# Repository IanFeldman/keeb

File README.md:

# A minimal ergo keyboard
Low profile, split, ortholinear, 34-key layout staggered to my natural finger rest positions. Designed for Gateron KS-33 Red swiches and DSA keycaps.
See write-up [here](https://ianfeldman.dev/projects/keyboard/).
<br><br>

## Features
- N-key rollover
- Efficient matrixless polling
- Lightweight and portable
- Serial communication between splits
- USB-C host connection

## Hardware Build Instructions
- Order and assemble PCB's
  - Reflow recommended for all surface mount components except SPI headers, TRRS jack, and crystal oscillator.
  - On hardware version 1.1, there are duplicate C2 and C3 traces. Only solder one C2 and one C3.
- Configure programming setup using In-system programmer (ensure shared ground)
- Power on PCB through USB-C connector
<br><br> _Note: only one PCB can be flashed at a time_

## Software Build and Flash Instructions (Linux)
```sh
# Install dependencies
sudo apt install gcc-avr avr-libc avrdude make

# Clone this repo
git clone https://github.com/IanFeldman/keeb.git
cd keeb

# Compile left or right half
make [left] [right]

# Update makefile targets 'fuses' and 'flash' as needed for your ISP device
# Set fuses with ISP (first time only)
make fuses

# Flash keyboard with ISP
make flash
```

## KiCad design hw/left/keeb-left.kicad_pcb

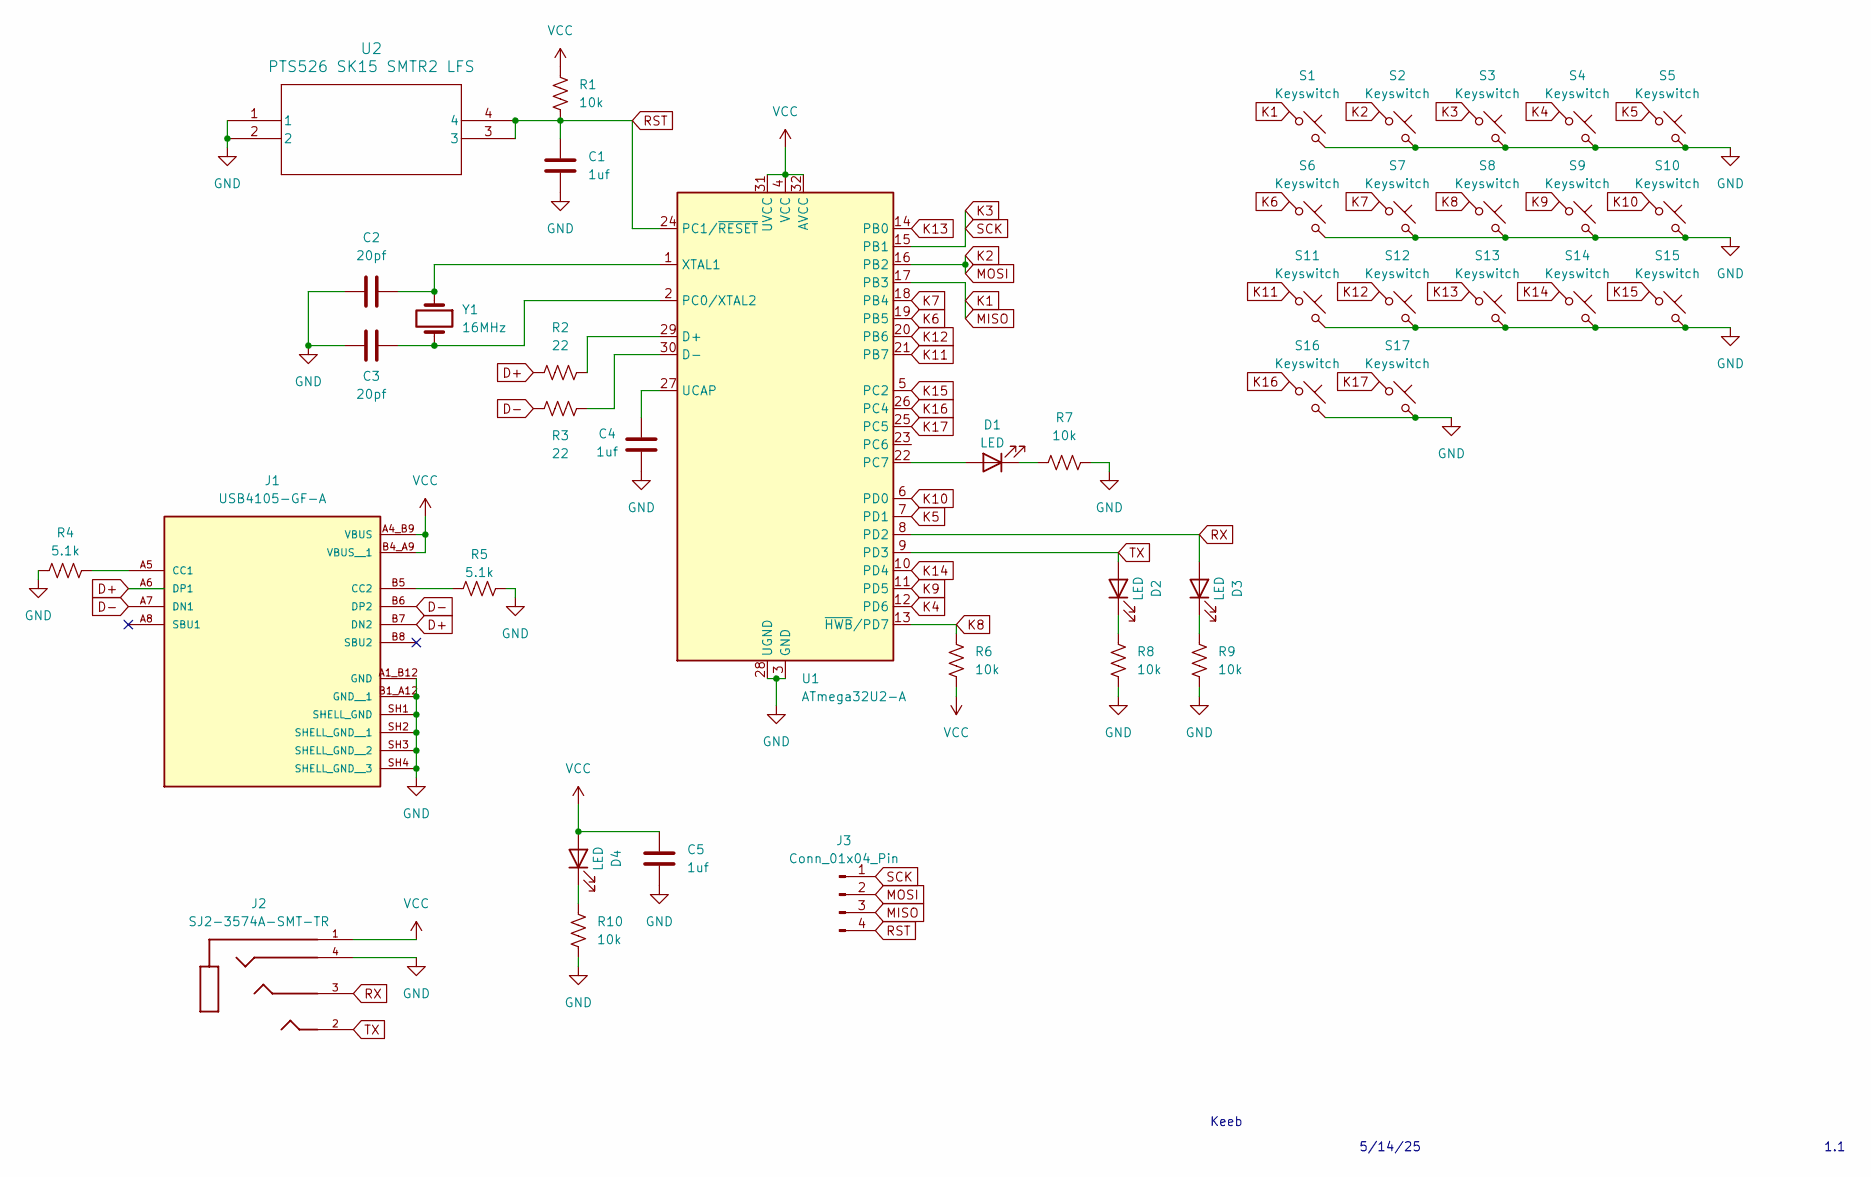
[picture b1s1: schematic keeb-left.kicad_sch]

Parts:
C1, C4, C5: 1uf; C_0805_2012Metric
C2, C3: 20pf; C_0805_2012Metric
D1, D2, D3, D4: LED; LED_0805_2012Metric
J1: USB4105-GF-A; GCT_USB4105-GF-A; PARTREV B4
J2: SJ2-3574A-SMT-TR; SAMESKY_SJ2-3574A-SMT-TR; PARTREV 1.05
J3: Conn_01x04_Pin; PinSocket_1x04_P2.54mm_Vertical_SMD_Pin1Right
R1, R6, R7, R8, R9, R10: 10k; R_0805_2012Metric
R2, R3: 22; R_0805_2012Metric
R4, R5: 5.1k; R_0805_2012Metric
S1, S2, S3, S4, S5, S6, S7, S8, S9, S10, S11, S12, S13, S14, S15, S16, S17: Keyswitch; SW_Gateron_LowProfile_THT_New
U1: ATmega32U2-A; TQFP-32_7x7mm_P0.8mm
U2: PTS526 SK15 SMTR2 LFS; SMT_FS
Y1: 16MHz; XTAL_ECS-160-20-5PX-TR

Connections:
D+: J1.A6 (DP1), J1.B7 (DN2), R2.1
D-: J1.A7 (DN1), J1.B6 (DP2), R3.1
GND: C1.2, C2.1, C3.2, C4.1, C5.1, J1.A1_B12 (GND), J1.B1_A12 (GND__1), J1.SH1 (SHELL_GND), J1.SH2 (SHELL_GND__1), J1.SH3 (SHELL_GND__2), J1.SH4 (SHELL_GND__3), J2.4, R4.1, R5.2, R7.1, R8.1, R9.1, R10.1, S1.2, S2.2, S3.2, S4.2, S5.2, S6.2, S7.2, S8.2, S9.2, S10.2, S11.2, S12.2, S13.2, S14.2, S15.2, S16.2, S17.2, U1.3 (GND), U1.28 (UGND), U2.1, U2.2
K1: J3.3, S1.1, U1.17 (PB3)
K2: J3.2, S2.1, U1.16 (PB2)
K3: J3.1, S3.1, U1.15 (PB1)
K4: S4.1, U1.12 (PD6)
K5: S5.1, U1.7 (PD1)
K6: S6.1, U1.19 (PB5)
K7: S7.1, U1.18 (PB4)
K8: R6.2, S8.1, U1.13 (~HWB/PD7)
K9: S9.1, U1.11 (PD5)
K10: S10.1, U1.6 (PD0)
K11: S11.1, U1.21 (PB7)
K12: S12.1, U1.20 (PB6)
K13: S13.1, U1.14 (PB0)
K14: S14.1, U1.10 (PD4)
K15: S15.1, U1.5 (PC2)
K16: S16.1, U1.26 (PC4)
K17: S17.1, U1.25 (PC5)
unnamed: D1.2 (A), U1.22 (PC7)
unnamed: D1.1 (K), R7.2
unnamed: D2.1 (K), R8.2
unnamed: D3.1 (K), R9.2
unnamed: D4.1 (K), R10.2
unnamed: J1.A5 (CC1), R4.2
unnamed: J1.B5 (CC2), R5.1
unnamed: R2.2, U1.29 (D+)
unnamed: R3.2, U1.30 (D-)
unnamed: C3.1, U1.2 (PC0/XTAL2), Y1.2
unnamed: C4.2, U1.27 (UCAP)
unnamed: C2.2, U1.1 (XTAL1), Y1.1
RST: C1.1, J3.4, R1.2, U1.24 (PC1/~RESET), U2.3, U2.4
RX: D3.2 (A), J2.3, U1.8 (PD2)
TX: D2.2 (A), J2.2, U1.9 (PD3)
VCC: C5.2, D4.2 (A), J1.A4_B9 (VBUS), J1.B4_A9 (VBUS__1), J2.1, R1.1, R6.1, U1.4 (VCC), U1.31 (UVCC), U1.32 (AVCC)

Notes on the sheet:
1.1
Keeb
5/14/25

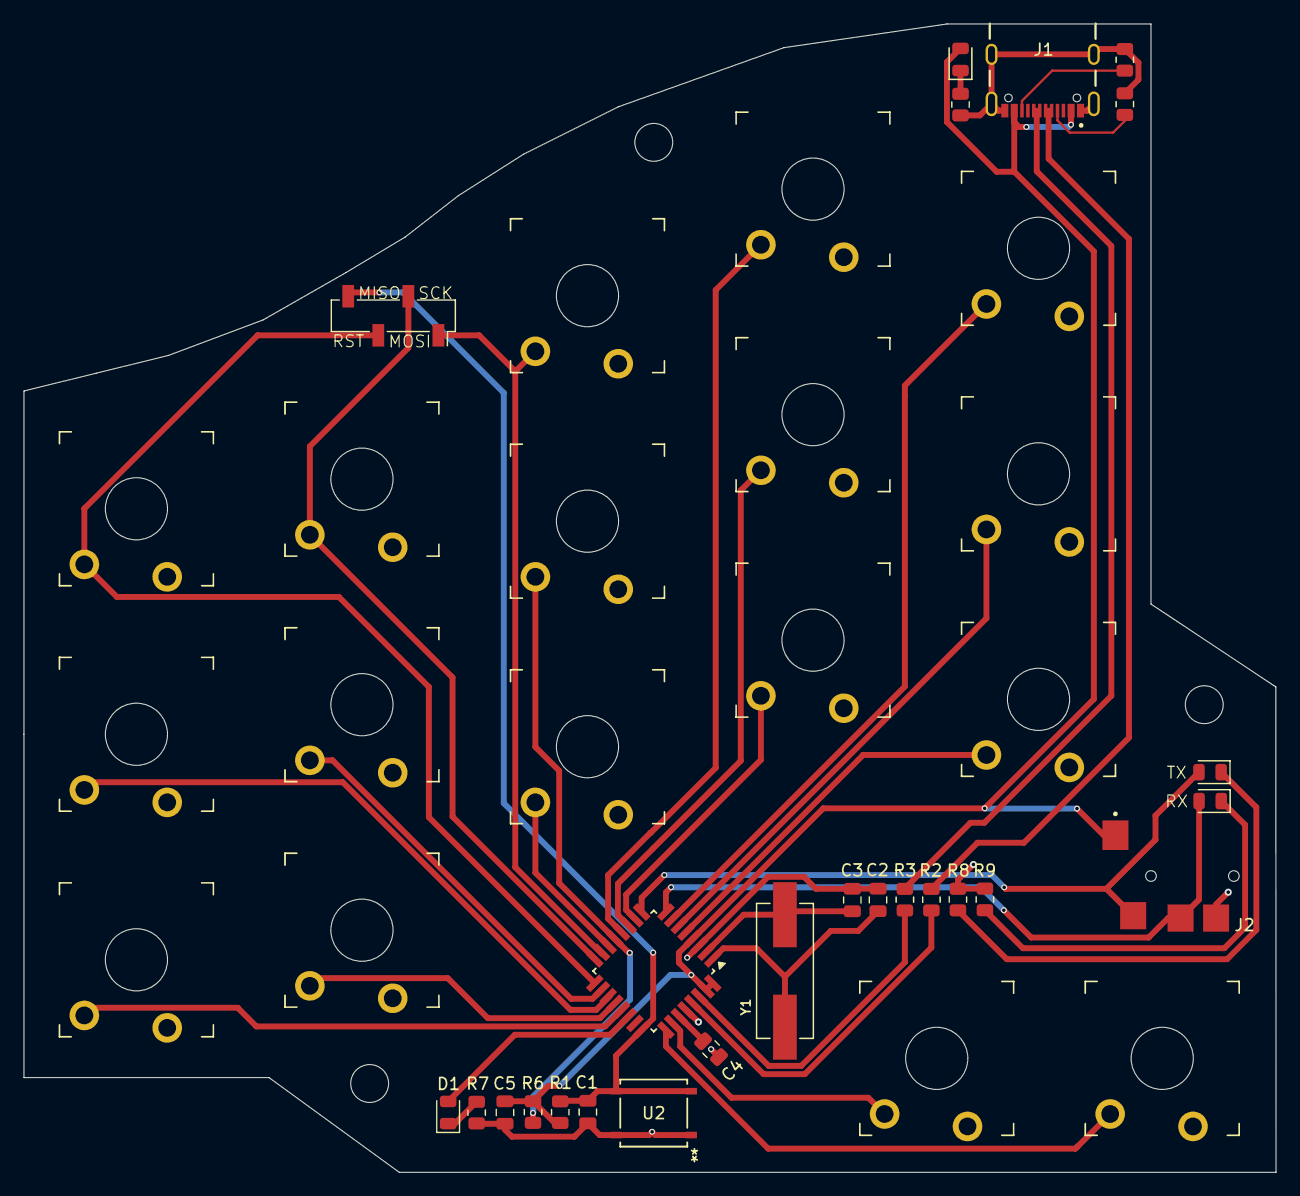
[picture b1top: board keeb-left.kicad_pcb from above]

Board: 2 copper layers, 105.8 x 97.0 mm, 42 parts (0 on the bottom side), 36 nets.

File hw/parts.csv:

Identifier,Part Number,Link,Unit Quantity,Total Quantity,Description,,Identifier,Digikey Part Number,Unit Quantity,Total Quantity,Description
U1,ATMEGA16U2-AU-ND,link,1,2,mcu,,U1,ATMEGA16U2-AU-ND,1,2,mcu
Y1,XC1282CT-ND,link,1,2,crystal,,Y1,XC1282CT-ND,1,2,16Mhz crystal
J1,2073-USB4105-GF-ACT-ND ,link,1,2,usbc connector,,J1,2073-USB4105-GF-ACT-ND ,1,2,usbc connector
J2,CP-SJ2-3574A-SMT-CT-ND,link,1,2,trrs connector,,J2,CP-SJ2-3574A-SMT-CT-ND,1,2,trrs connector
J3,WM20565CT-ND,link,1,2,pins,,J3,WM20565CT-ND,1,2,pins
SW1,CKN12221-1-ND,link,1,2,push button,,SW1,CKN12221-1-ND,1,2,push button
D1...D4,475-LSR976-NR-1CT-ND,link,4,8,leds,,"D1, D2, D3, D4",475-LSR976-NR-1CT-ND,4,8,leds
"R1, R6",RMCF0805FT10K0CT-ND,link,2,4,10kohm,,"R1, R6, R7, R8, R9, R10",RMCF0805FT10K0CT-ND,6,12,10kohm
"R2, R3",RMCF0805JT22R0CT-ND,link,2,4,22ohm,,"R2, R3",RMCF0805JT22R0CT-ND,2,4,22ohm
"R4, R5",RMCF0805JT5K10CT-ND,link,2,4,5.1kohm,,"R4, R5",RMCF0805JT5K10CT-ND,2,4,5.1kohm
R7...R10,RMCF0805JT220RCT-ND,link,4,8,220ohm,,"C1, C4, C5",311-1365-1-ND,3,6,1uf
extra R7...R10,RMCF0805JT150RCT-ND,,,8,150ohm,,"C2, C3",311-3614-1-ND,2,4,20pf
"C1, C4, C5",311-1365-1-ND,link,3,6,1uf,,,,,,
"C2, C3",311-3614-1-ND,link,2,4,20pf,,,,,,

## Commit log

2025-04-19 Add hw files
2025-04-19 Add right board
2025-04-19 Remove original
2025-04-21 Hardware revision
2025-04-21 Add lufa
2025-04-21 Clean up
2025-04-21 Fix spacing
2025-04-29 Fix avrdude cmds, add debug flash
2025-04-30 Add uart
2025-04-30 Add device
2025-04-30 Small changes
2025-04-30 Begin parsing keys
2025-04-30 Implement n key rollover hid
2025-04-30 Peripheral send key report
2025-04-30 Startup delay
2025-04-30 Fix report send logic
2025-05-01 Reset key buffer and update interrupt handling
2025-05-01 Increase uart speed
2025-05-01 Report over uart works!
2025-05-01 Add basic key scancodes
2025-05-02 Fix keypress logic
2025-05-02 Support layer key
2025-05-03 Refactor
2025-05-03 Change layer info send to toggle
2025-05-03 Fix layer breaking bug
2025-05-05 Update base layer keycodes
2025-05-05 Add upper layer
2025-05-06 Add layer info byte to report
2025-05-06 Pass in references to uart functions
2025-05-12 Layer key consistency
2025-05-12 Add layer hold to make layer key press more forgiving
2025-05-12 Enable led on layer press
2025-05-14 Update hardware
2025-05-14 Fix parts list
2025-05-14 Reorganize
2025-05-14 Add meta key
2025-06-11 Update README.md
    Add build dependencies
2025-06-11 Update README.md
    Change link format
